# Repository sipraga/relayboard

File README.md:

# relayboard

it looks like this

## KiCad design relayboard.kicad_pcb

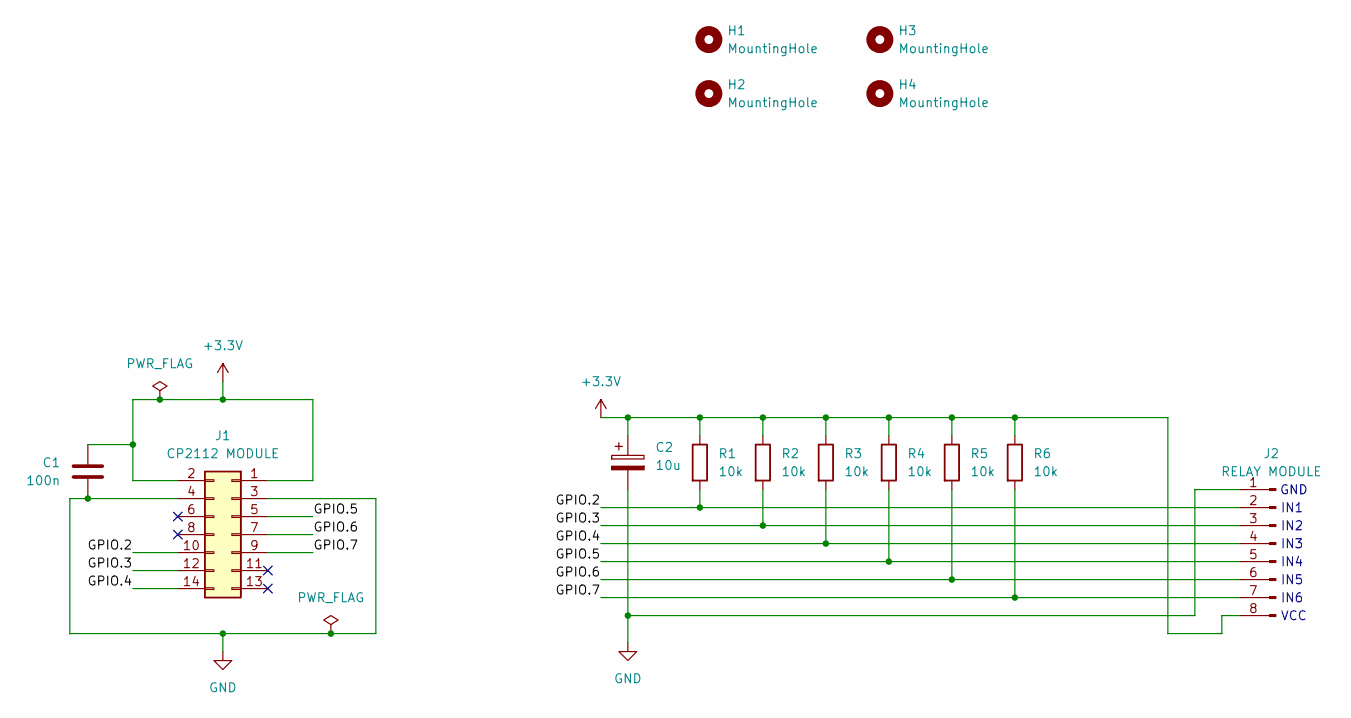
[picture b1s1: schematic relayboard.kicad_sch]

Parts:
C1: 100n; C_Disc_D5.0mm_W2.5mm_P5.00mm
C2: 10u; CP_Radial_D5.0mm_P2.50mm
H1, H2, H3, H4: MountingHole; MountingHole_2.7mm_M2.5
J1: CP2112 MODULE; PinSocket_2x07_P2.54mm_Vertical
J2: RELAY MODULE; PinHeader_1x08_P2.54mm_Vertical
R1, R2, R3, R4, R5, R6: 10k; R_Axial_DIN0207_L6.3mm_D2.5mm_P7.62mm_Horizontal

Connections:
+3.3V: C1.1, C2.1, J1.1, J1.2, J2.8, R1.1, R2.1, R3.1, R4.1, R5.1, R6.1
/GPIO.2: J1.10, J2.2, R1.2
/GPIO.3: J1.12, J2.3, R2.2
/GPIO.4: J1.14, J2.4, R3.2
/GPIO.5: J1.5, J2.5, R4.2
/GPIO.6: J1.7, J2.6, R5.2
/GPIO.7: J1.9, J2.7, R6.2
GND: C1.2, C2.2, J1.3, J1.4, J2.1

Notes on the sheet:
IN3
IN6
IN4
VCC
GND
IN1
IN5
IN2

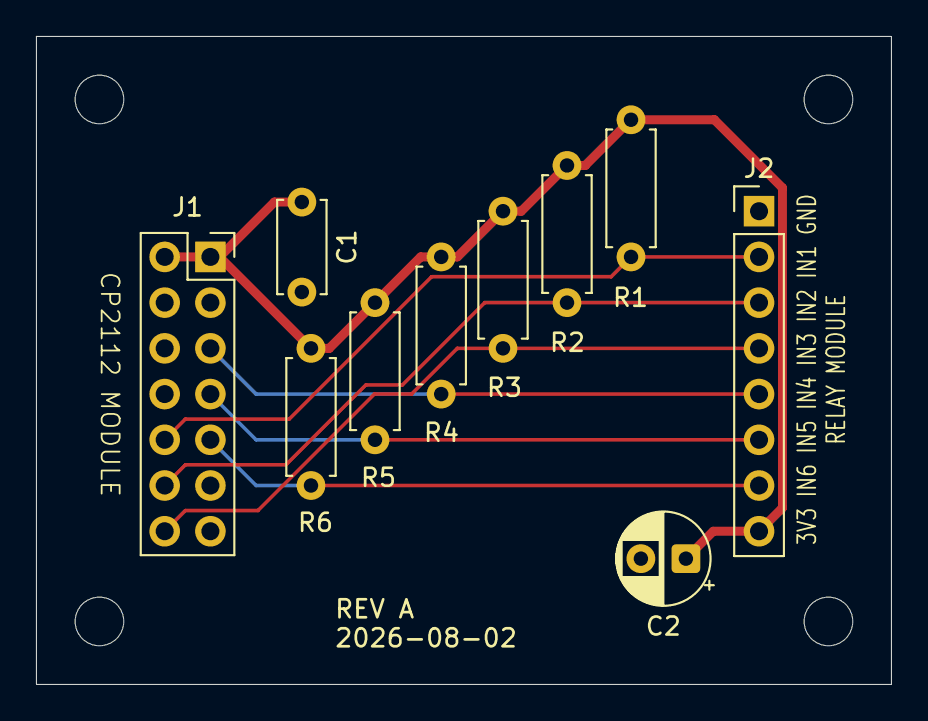
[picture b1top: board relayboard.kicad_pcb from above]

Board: 2 copper layers, 47.5 x 36.0 mm, 14 parts (0 on the bottom side), 8 nets.
